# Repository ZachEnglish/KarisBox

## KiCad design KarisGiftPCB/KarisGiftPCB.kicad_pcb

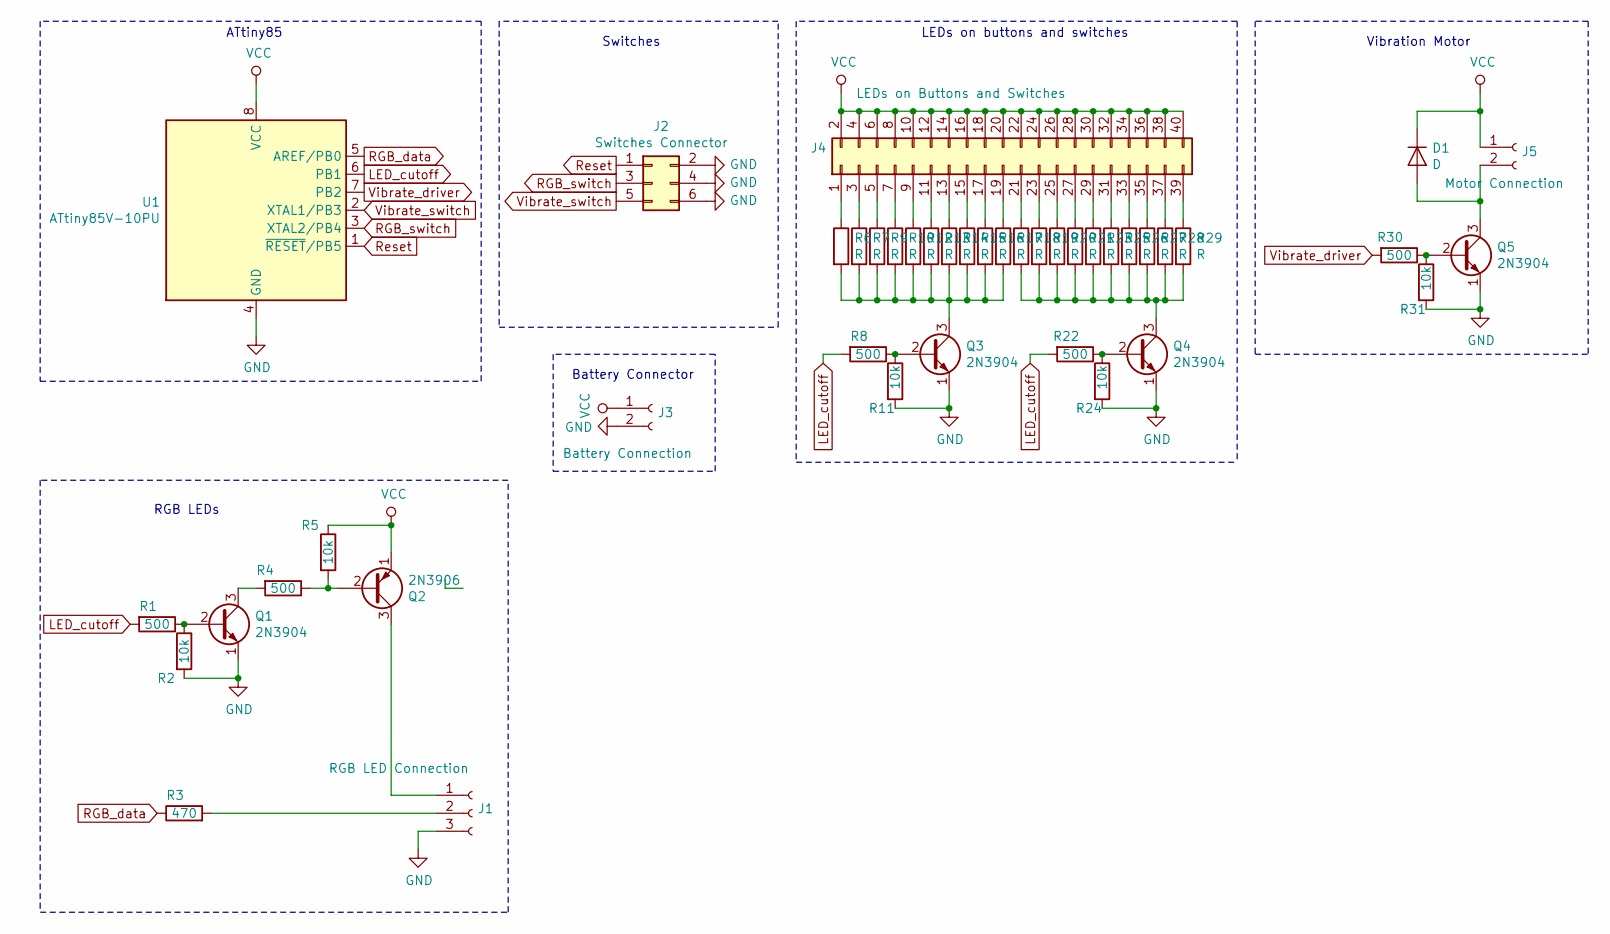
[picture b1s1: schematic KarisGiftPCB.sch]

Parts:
D1: D; D_DO-41_SOD81_P10.16mm_Horizontal
J1: RGB LED Connection; PinSocket_1x03_P2.54mm_Vertical
J2: Switches Connector; PinSocket_2x03_P2.54mm_Vertical
J3: Battery Connection; PinSocket_1x02_P2.54mm_Vertical
J4: LEDs on Buttons and Switches; PinSocket_2x20_P2.54mm_Vertical
J5: Motor Connection; PinSocket_1x02_P2.54mm_Vertical
Q1, Q3, Q4, Q5: 2N3904; TO-92_Inline
Q2: 2N3906; TO-92_Inline
R1, R4, R8, R22, R30: 500; R_Axial_DIN0207_L6.3mm_D2.5mm_P10.16mm_Horizontal
R2, R5, R11, R24, R31: 10k; R_Axial_DIN0207_L6.3mm_D2.5mm_P10.16mm_Horizontal
R3: 470; R_Axial_DIN0207_L6.3mm_D2.5mm_P10.16mm_Horizontal
R6, R7, R9, R10, R12, R13, R14, R15, R16, R17, R18, R19, R20, R21, R23, R25, R26, R27, R28, R29: R; R_Axial_DIN0207_L6.3mm_D2.5mm_P10.16mm_Horizontal
U1: ATtiny85V-10PU; DIP-8_W7.62mm

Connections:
GND: J1.3, J2.2, J2.4, J2.6, J3.2, Q1.1 (E), Q3.1 (E), Q4.1 (E), Q5.1 (E), R2.2, R11.2, R24.2, R31.2, U1.4 (GND); also elsewhere on the board
LED_cutoff: R1.2, R8.2, R22.2, U1.6 (PB1); also elsewhere on the board
unnamed 2: D1.2 (A), J5.2, Q5.3 (C); also elsewhere on the board
unnamed 3: J1.1, Q2.3 (C); also elsewhere on the board
unnamed 4: J1.2, R3.2; also elsewhere on the board
unnamed: J2.1, U1.1 (~RESET~/PB5)
unnamed: J2.3, U1.3 (XTAL2/PB4)
unnamed: J2.5, U1.2 (XTAL1/PB3)
unnamed: J4.1, R6.1
unnamed: J4.3, R7.1
unnamed: J4.5, R9.1
unnamed: J4.7, R10.1
unnamed: J4.9, R12.1
unnamed: J4.11, R13.1
unnamed: J4.13, R14.1
unnamed: J4.15, R15.1
unnamed: J4.17, R16.1
unnamed: J4.19, R17.1
unnamed: J4.21, R18.1
unnamed: J4.23, R19.1
unnamed: J4.25, R20.1
unnamed: J4.27, R21.1
unnamed: J4.29, R23.1
unnamed: J4.31, R25.1
unnamed: J4.33, R26.1
unnamed: J4.35, R27.1
unnamed: J4.37, R28.1
unnamed: J4.39, R29.1
unnamed: Q1.2 (B), R1.1, R2.1
unnamed: Q1.3 (C), R4.2
unnamed: Q2.2 (B), R4.1, R5.2
unnamed: Q3.2 (B), R8.1, R11.1
unnamed: Q3.3 (C), R6.2, R7.2, R9.2, R10.2, R12.2, R13.2, R14.2, R15.2, R16.2, R17.2
unnamed: Q4.2 (B), R22.1, R24.1
unnamed: Q4.3 (C), R18.2, R19.2, R20.2, R21.2, R23.2, R25.2, R26.2, R27.2, R28.2, R29.2
unnamed: Q5.2 (B), R30.1, R31.1
RGB_data: R3.1, U1.5 (AREF/PB0); also elsewhere on the board
VCC: D1.1 (K), J3.1, J4.2, J4.4, J4.6, J4.8, J4.10, J4.12, J4.14, J4.16, J4.18, J4.20, J4.22, J4.24, J4.26, J4.28, J4.30, J4.32, J4.34, J4.36, J4.38, J4.40, J5.1, Q2.1 (E), R5.1, U1.8 (VCC); also elsewhere on the board
Vibrate_driver: R30.2, U1.7 (PB2); also elsewhere on the board

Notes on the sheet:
ATtiny85
Switches
LEDs on buttons and switches
Vibration Motor
RGB LEDs
Battery Connector

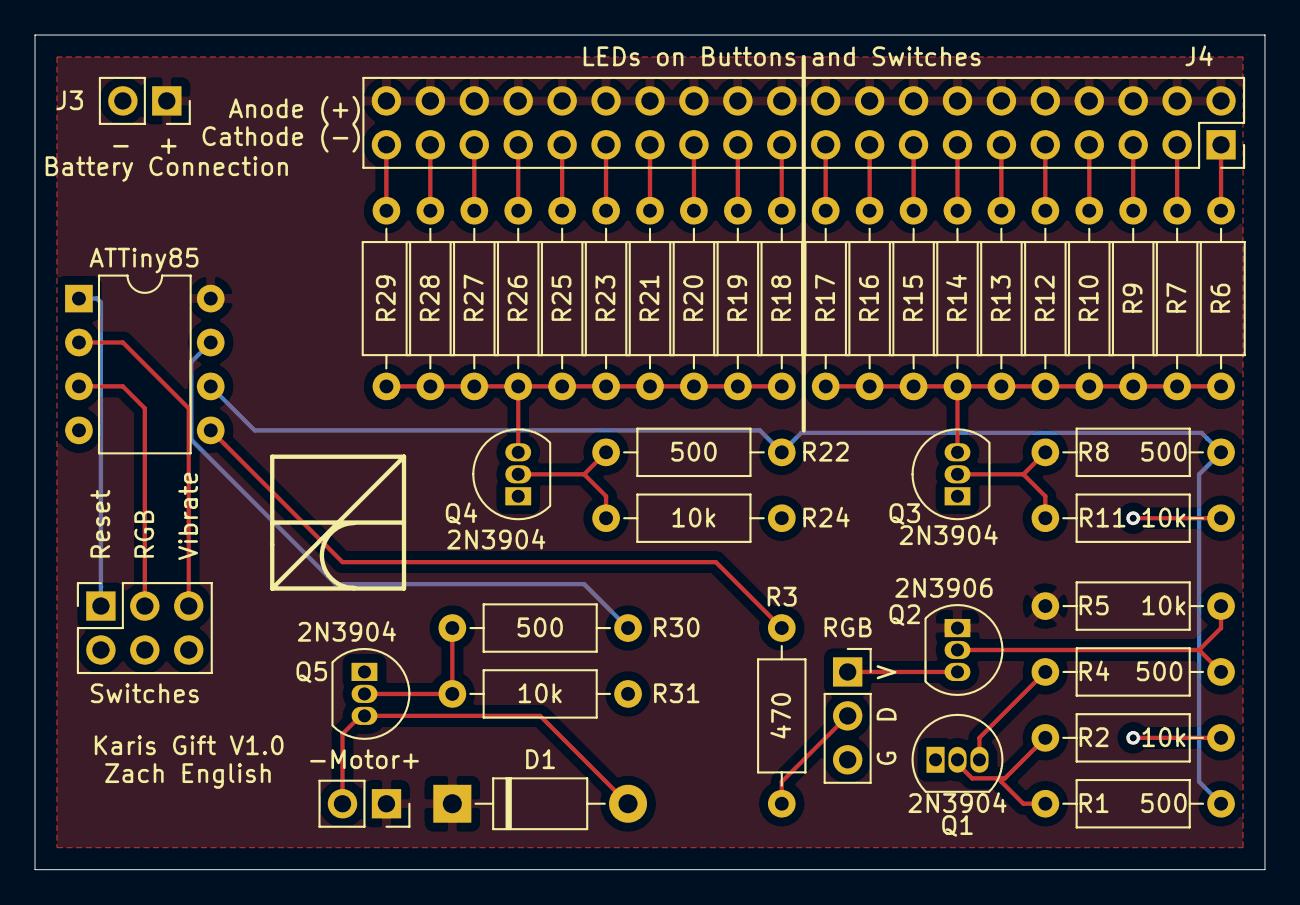
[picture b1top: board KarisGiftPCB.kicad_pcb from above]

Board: 2 copper layers, 71.1 x 48.3 mm, 43 parts (0 on the bottom side), 39 nets.

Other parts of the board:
-Motor+: Motor Connection; PinSocket_1x02_P2.54mm_Vertical
ATTiny85: ATtiny85V-10PU; DIP-8_W7.62mm
RGB: RGB LED Connection; PinSocket_1x03_P2.54mm_Vertical
Switches: Switches; PinSocket_2x03_P2.54mm_Vertical

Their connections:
GND: ATTiny85.4, RGB.3, Switches.2, Switches.4, Switches.6; also elsewhere on the board
LED_cutoff: ATTiny85.6; also elsewhere on the board
unnamed 2: -Motor+.2; also elsewhere on the board
unnamed 3: RGB.1; also elsewhere on the board
unnamed 4: RGB.2; also elsewhere on the board
RGB_data: ATTiny85.5; also elsewhere on the board
RGB_switch: ATTiny85.3, Switches.3
Reset: ATTiny85.1, Switches.1
VCC: -Motor+.1, ATTiny85.8; also elsewhere on the board
Vibrate_driver: ATTiny85.7; also elsewhere on the board
Vibrate_switch: ATTiny85.2, Switches.5

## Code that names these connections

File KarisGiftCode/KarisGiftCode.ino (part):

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#define NUMBER_OF_RGB_LEDS 7

#define PIN_RGB            0 //data line out to the RGB LEDs
#define PIN_LED_CUTOFF     1 //signal to all LED and RGB LED transistors
#define PIN_VIBRATE_DRIVE  2 //signal to vibration motor transistor
#define PIN_VIBRATE_SWITCH 3 //input from button/switch to initiate vibrate sequence
#define PIN_RGB_SWITCH     4 //input form button/switch to change RGB state


#define INACTIVE_TIME (90UL*1000UL) //90 seconds converted to milliseconds
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void setup() {
  //initialize pins
  pinMode(PIN_RGB, OUTPUT);
  pinMode(PIN_LED_CUTOFF, OUTPUT);
  pinMode(PIN_VIBRATE_DRIVE, OUTPUT);
  pinMode(PIN_VIBRATE_SWITCH, INPUT_PULLUP);
  pinMode(PIN_RGB_SWITCH, INPUT_PULLUP);

  //save power by disabling the anolog to digital converter, not using it anyway
  adc_disable();

  digitalWrite(PIN_LED_CUTOFF, HIGH); //HIGH leaves the LEDs able to turn on. LOW turns off the circuit.

  rgbStrip.begin(); //initialize the RGB strip
  rgbStrip.show(); //push out the empty buffer so the strip goes clear (in case it had something in it)
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bool rgb_button_has_been_pressed() {
  static bool last_rgb_button_state = false;
  //Get the state of the button. Invert the logic to make true/high when pressed
  bool current_rgb_button_state = !digitalRead(PIN_RGB_SWITCH);
  bool pressed;

  //if it is pressed now and it wasn't last time we checked...
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bool vibrate_button_has_been_pressed() {
  static bool last_vibrate_button_state = false;
  //Get the state of the button. Invert the logic to make true/high when pressed
  bool current_vibrate_button_state = !digitalRead(PIN_VIBRATE_SWITCH);
  bool pressed;

  if (current_vibrate_button_state && !last_vibrate_button_state) {
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//INPUT.
void turn_off_outputs() {
  pinMode(PIN_RGB, INPUT);
  pinMode(PIN_LED_CUTOFF, INPUT);
  pinMode(PIN_VIBRATE_DRIVE, INPUT);
}

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
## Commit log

2021-01-08 Initial commit. Work in progress, need to update some transitors to PNP's.
2021-01-09 First pass on the code. Playing with options and the mircocontroller.
2021-01-09 Updated RGB LEDs block to not move ground reference on data signal.
    Added pull up/down resisters for transistors.
2021-01-09 Added word file with R values for resistors.
2021-01-11 I can't believe it works! The code works!
2021-01-11 Made RGB state roll over at top.
2021-01-12 Updated schematic to use just one PNP transistor for RGB LEDs.
    Started the long process of cleaning up the code.
2021-01-12 More refactoring and cleanup
2021-01-12 Fixed backwards PNP transistor running the RGB LEDs (Thanks Ron!)
    Some more code cleanup.
2021-01-12 Mirrored PNP to make schematic less ugly
2021-01-12 Started work on addressing the RGB timing code.
2021-01-13 Added second schematic in prep for layout. Replaced parts with jumpers.
2021-01-13 Added footprints to all parts in schematic.
2021-01-13 Made new Kicad project for PCB schematic and layout. Started layout.
2021-01-13 Made some progress on PCB layout. "Some" as in, kinda started.
2021-01-14 Layout mostly done, just need wires, copper areas, and edge cuts.
2021-01-14 Finished board layout. Generated Gerber files.
2021-01-14 Added some images.
    Noted that I wrote Aaron instead of Alex. Need to fix.
2021-01-14 Updated names for correctness and spelling.
2021-01-15 First real pass at attempting better RGB timing control.
    Not clean. Untested.
2021-01-15 Got the RGB states working! Stupid C standard and declaring variables in switch statements. Gah. Faught that quite a while.
    Still need to do more cleaning of code.
    Also, on the color wipes the RGB strip sometimes misses the first pixel
    on its first pass and catches it later. Not horrible, but catches your
    eye.
2021-01-15 Cleaning up some code.
2021-01-15 Updated silkscreen and some code cleanup
2021-01-16 Lot's of cleanup on code and one bug fix on the vibrate button logic.
    Untested in HW, but sure looks better in SW ;-)
2021-01-17 It works! Added slow rainbow RGB mode. Ran auto-formatter.
2021-01-18 Code cleanup and reduction. Removed uneccessary complexity and standardized naming a bit.
2021-01-18 It works! Tested on HW and it functions. Ran auto-format tool in Arduino
2021-01-18 Got rid of one more global
2021-02-07 Printed out again to submit for order
2021-02-07 Now sketch saves state of current rgb mode to eeprom.
    Fixed bug where vibrate motor would always go off 30 seconds into sketch.
    Fixed minor naming inconsistancies.
2021-10-14 Ready for prime time!
